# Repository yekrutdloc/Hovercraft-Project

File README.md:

# Line-following Hovercraft
School project embedded systems, web, Arduino

Functioning Hovercraft system

Contains documentation

Uses FreeRTOS, PID-library and Arduino

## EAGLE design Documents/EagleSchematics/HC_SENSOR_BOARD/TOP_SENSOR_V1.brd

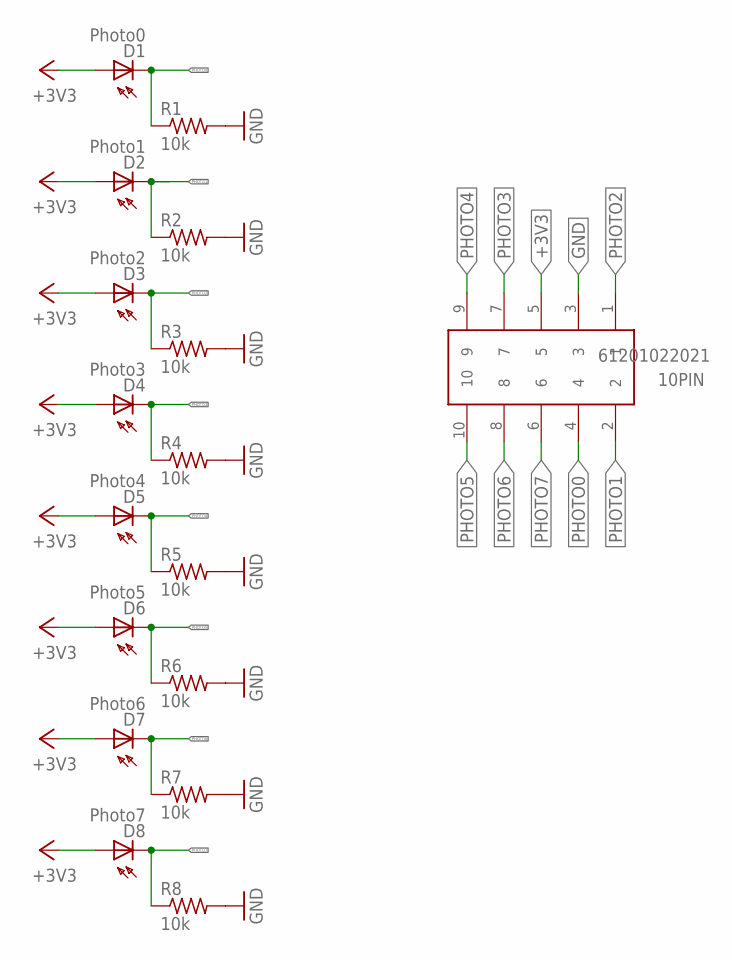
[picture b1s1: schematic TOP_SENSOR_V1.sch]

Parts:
10PIN: 61201022021
D1: Photo0; BPX65
D2: Photo1; BPX65
D3: Photo2; BPX65
D4: Photo3; BPX65
D5: Photo4; BPX65
D6: Photo5; BPX65
D7: Photo6; BPX65
D8: Photo7; BPX65
R1, R2, R3, R4, R5, R6, R7, R8: 10k; 0207/10

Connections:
+3V3: 10PIN.5, D1.A, D2.A, D3.A, D4.A, D5.A, D6.A, D7.A, D8.A
GND: 10PIN.3, R1.2, R2.2, R3.2, R4.2, R5.2, R6.2, R7.2, R8.2
PHOTO0: 10PIN.4, D1.K (C), R1.1
PHOTO1: 10PIN.2, D2.K (C), R2.1
PHOTO2: 10PIN.1, D3.K (C), R3.1
PHOTO3: 10PIN.7, D4.K (C), R4.1
PHOTO4: 10PIN.9, D5.K (C), R5.1
PHOTO5: 10PIN.10, D6.K (C), R6.1
PHOTO6: 10PIN.8, D7.K (C), R7.1
PHOTO7: 10PIN.6, D8.K (C), R8.1

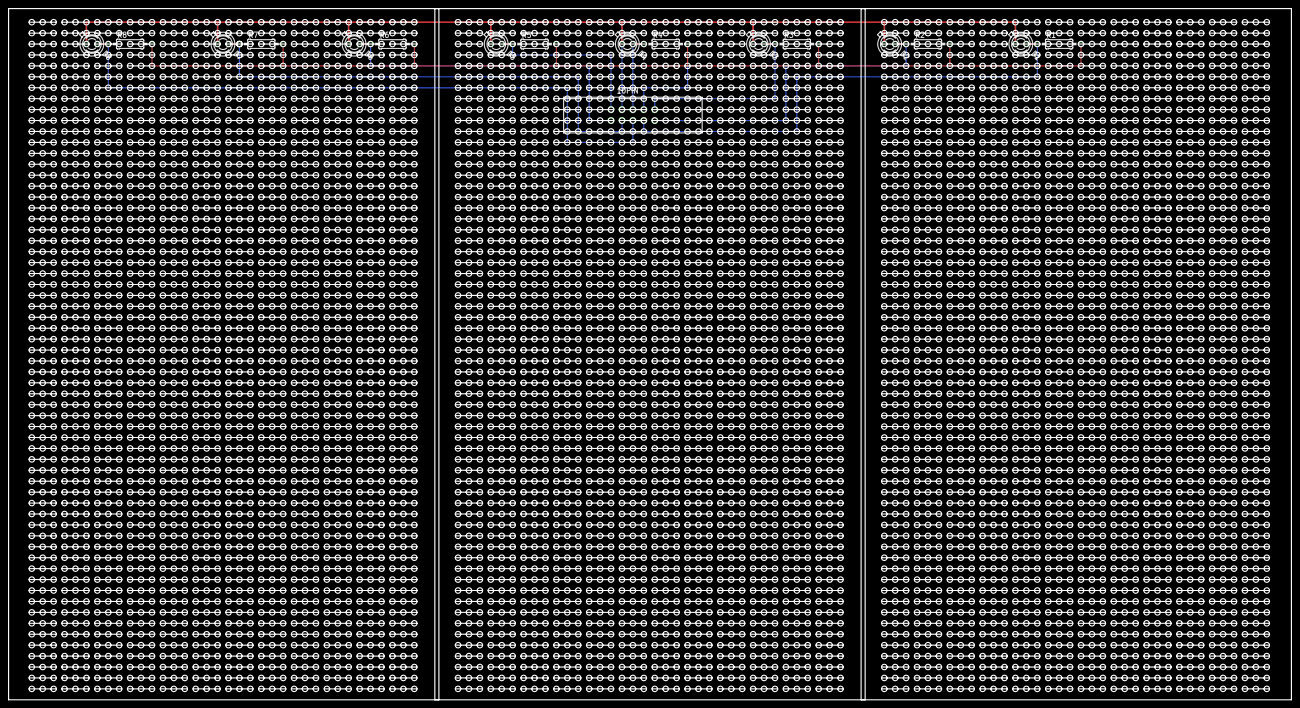
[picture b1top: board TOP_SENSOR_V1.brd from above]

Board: 2 copper layers, 298.1 x 160.6 mm, 17 parts (0 on the bottom side), 10 nets.

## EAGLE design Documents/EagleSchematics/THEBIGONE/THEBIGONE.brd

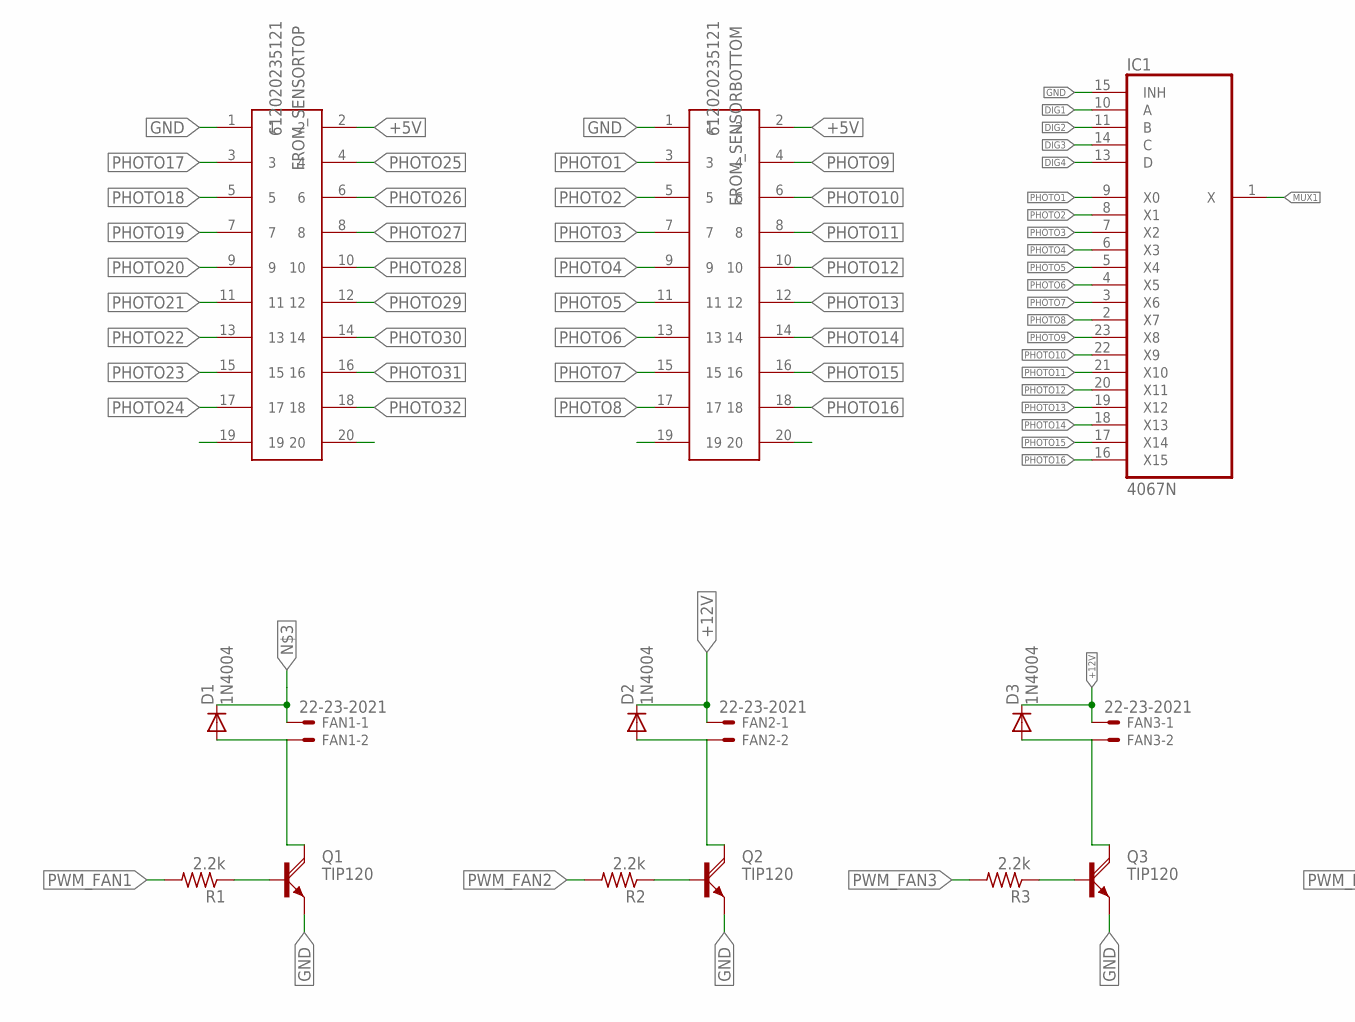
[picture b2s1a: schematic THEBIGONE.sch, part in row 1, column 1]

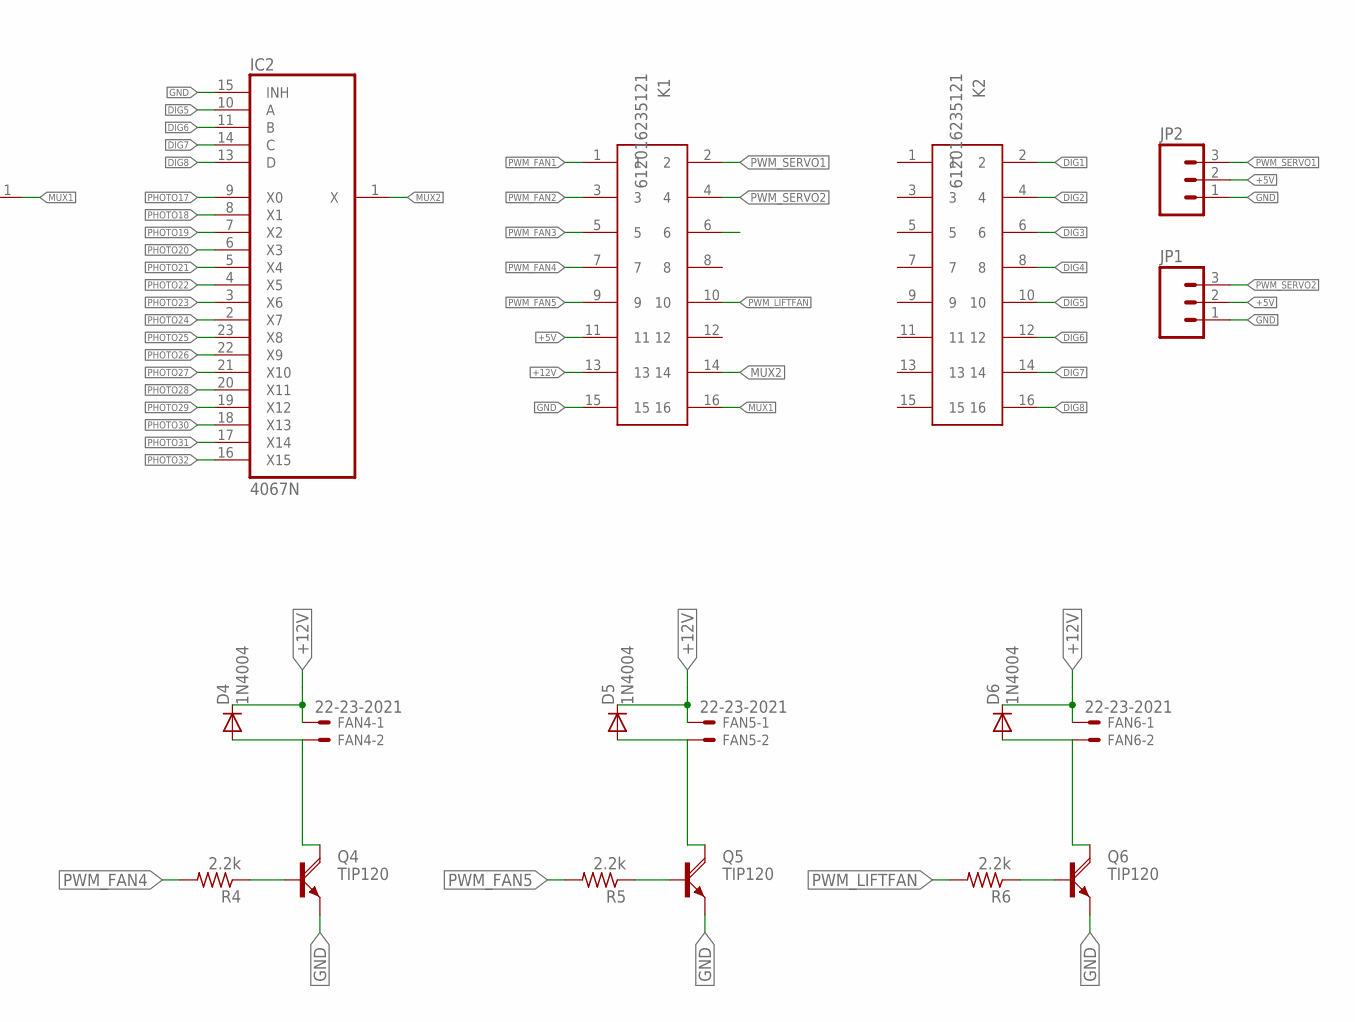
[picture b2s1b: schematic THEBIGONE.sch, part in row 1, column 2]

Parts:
D1, D2, D3, D4, D5, D6: 1N4004; DO41-10
FAN1, FAN2, FAN3, FAN4, FAN5, FAN6: 22-23-2021
FROM_SENSORBOTTOM: 612020235121
FROM_SENSORTOP: 612020235121
IC1, IC2: 4067N; DIL24-6
JP1, JP2: M03JST-PTH-VERT; JST-3-PTH-VERT
K1, K2: 612016235121
Q1, Q2, Q3, Q4, Q5, Q6: TIP120; TO220AH
R1, R2, R3, R4, R5, R6: 2.2k; 0204/7

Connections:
+5V: FROM_SENSORBOTTOM.2, FROM_SENSORTOP.2, JP1.2, JP2.2, K1.11
+12V: D1.C, D2.C, D3.C, FAN1.1, FAN2.1, FAN3.1, K1.13
DIG1: IC1.10 (A), K2.2
DIG2: IC1.11 (B), K2.4
DIG3: IC1.14 (C), K2.6
DIG4: IC1.13 (D), K2.8
DIG5: IC2.10 (A), K2.10
DIG6: IC2.11 (B), K2.12
DIG7: IC2.14 (C), K2.14
DIG8: IC2.13 (D), K2.16
GND: FROM_SENSORBOTTOM.1, FROM_SENSORTOP.1, IC1.15 (INH), IC2.15 (INH), JP1.1, JP2.1, K1.15, Q1.E, Q2.E, Q3.E, Q4.E, Q5.E, Q6.E
MUX1: IC1.1 (X), K1.16
MUX2: IC2.1 (X), K1.14
unnamed: D1.A, FAN1.2, Q1.C
unnamed: D2.A, FAN2.2, Q2.C
unnamed: Q1.B, R1.1
unnamed: Q2.B, R2.1
unnamed: D3.A, FAN3.2, Q3.C
unnamed: D4.A, FAN4.2, Q4.C
unnamed: D4.C, FAN4.1
unnamed: Q5.B, R5.1
unnamed: Q4.B, R4.1
unnamed: D5.A, FAN5.2, Q5.C
unnamed: D5.C, FAN5.1
unnamed: Q3.B, R3.1
unnamed: Q6.B, R6.1
unnamed: D6.A, FAN6.2, Q6.C
unnamed: D6.C, FAN6.1
PHOTO1: FROM_SENSORBOTTOM.3, IC1.9 (X0)
PHOTO2: FROM_SENSORBOTTOM.5, IC1.8 (X1)
PHOTO3: FROM_SENSORBOTTOM.7, IC1.7 (X2)
PHOTO4: FROM_SENSORBOTTOM.9, IC1.6 (X3)
PHOTO5: FROM_SENSORBOTTOM.11, IC1.5 (X4)
PHOTO6: FROM_SENSORBOTTOM.13, IC1.4 (X5)
PHOTO7: FROM_SENSORBOTTOM.15, IC1.3 (X6)
PHOTO8: FROM_SENSORBOTTOM.17, IC1.2 (X7)
PHOTO9: FROM_SENSORBOTTOM.4, IC1.23 (X8)
PHOTO10: FROM_SENSORBOTTOM.6, IC1.22 (X9)
PHOTO11: FROM_SENSORBOTTOM.8, IC1.21 (X10)
PHOTO12: FROM_SENSORBOTTOM.10, IC1.20 (X11)
PHOTO13: FROM_SENSORBOTTOM.12, IC1.19 (X12)
PHOTO14: FROM_SENSORBOTTOM.14, IC1.18 (X13)
PHOTO15: FROM_SENSORBOTTOM.16, IC1.17 (X14)
PHOTO16: FROM_SENSORBOTTOM.18, IC1.16 (X15)
PHOTO17: FROM_SENSORTOP.3, IC2.9 (X0)
PHOTO18: FROM_SENSORTOP.5, IC2.8 (X1)
PHOTO19: FROM_SENSORTOP.7, IC2.7 (X2)
PHOTO20: FROM_SENSORTOP.9, IC2.6 (X3)
PHOTO21: FROM_SENSORTOP.11, IC2.5 (X4)
PHOTO22: FROM_SENSORTOP.13, IC2.4 (X5)
PHOTO23: FROM_SENSORTOP.15, IC2.3 (X6)
PHOTO24: FROM_SENSORTOP.17, IC2.2 (X7)
PHOTO25: FROM_SENSORTOP.4, IC2.23 (X8)
PHOTO26: FROM_SENSORTOP.6, IC2.22 (X9)
PHOTO27: FROM_SENSORTOP.8, IC2.21 (X10)
PHOTO28: FROM_SENSORTOP.10, IC2.20 (X11)
PHOTO29: FROM_SENSORTOP.12, IC2.19 (X12)
PHOTO30: FROM_SENSORTOP.14, IC2.18 (X13)
PHOTO31: FROM_SENSORTOP.16, IC2.17 (X14)
PHOTO32: FROM_SENSORTOP.18, IC2.16 (X15)
PWM_FAN1: K1.1, R1.2
PWM_FAN2: K1.3, R2.2
PWM_FAN3: K1.5, R3.2
PWM_FAN4: K1.7, R4.2
PWM_FAN5: K1.9, R5.2
PWM_LIFTFAN: K1.10, R6.2
PWM_SERVO1: JP2.3, K1.2
PWM_SERVO2: JP1.3, K1.4
PWM_SERVO3: K1.6
VDD: IC1.24 (VDD), IC2.24 (VDD)
VSS: IC1.12 (VSS), IC2.12 (VSS)

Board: 2 copper layers, 32 parts (0 on the bottom side), 70 nets, no tracks yet.

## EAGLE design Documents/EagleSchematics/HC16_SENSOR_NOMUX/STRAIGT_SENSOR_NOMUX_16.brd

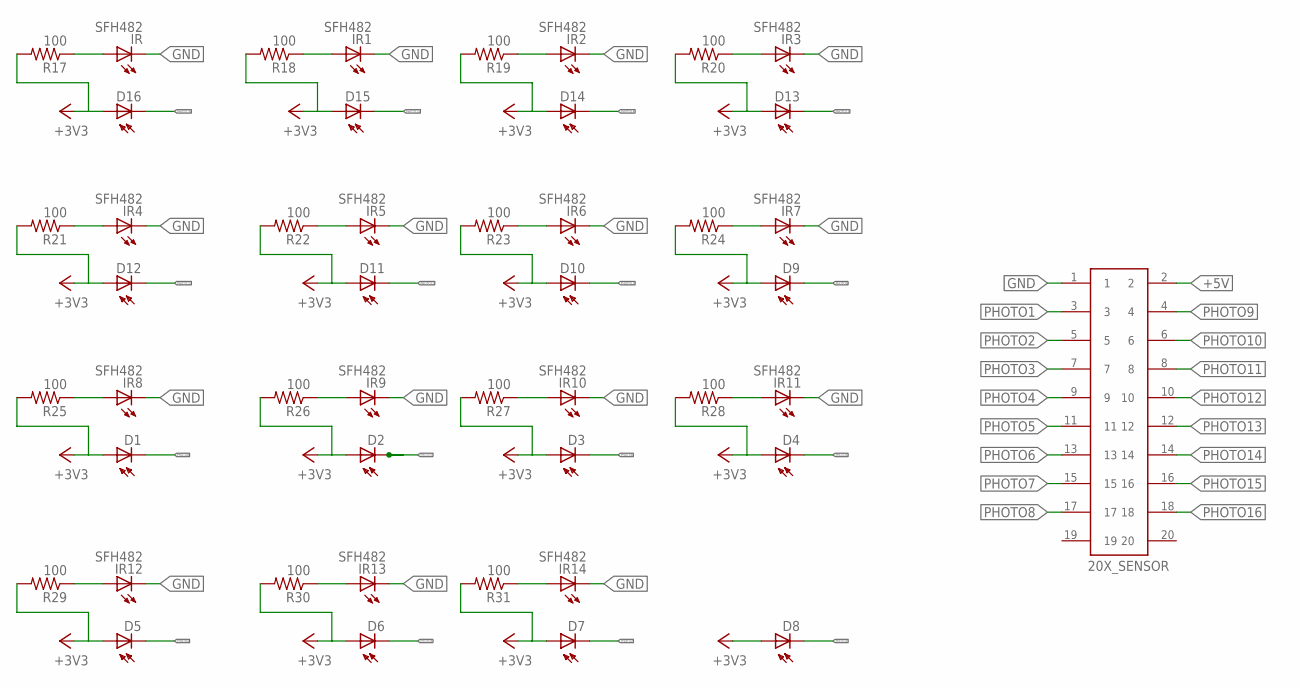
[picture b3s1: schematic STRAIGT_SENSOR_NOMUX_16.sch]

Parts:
20X_SENSOR: 61202022021
D1, D9, D10, D11, D12, D13, D14, D15, D16: Photo0; BPX65
D2: Photo1; BPX65
D3: Photo2; BPX65
D4: Photo3; BPX65
D5: Photo4; BPX65
D6: Photo5; BPX65
D7: Photo6; BPX65
D8: Photo7; BPX65
IR, IR1, IR2, IR3, IR4, IR5, IR6, IR7, IR8, IR9, IR10, IR11, IR12, IR13, IR14: SFH482
R17, R18, R19, R20, R21, R22, R23, R24, R25, R26, R27, R28, R29, R30, R31: 100; 0207/10

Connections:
+3V3: D1.A, D2.A, D3.A, D4.A, D5.A, D6.A, D7.A, D8.A, D9.A, D10.A, D11.A, D12.A, D13.A, D14.A, D15.A, D16.A, R17.2, R18.2, R19.2, R20.2, R21.2, R22.2, R23.2, R24.2, R25.2, R26.2, R27.2, R28.2, R29.2, R30.2, R31.2
+5V: 20X_SENSOR.2
GND: 20X_SENSOR.1, IR.K (C), IR1.K (C), IR2.K (C), IR3.K (C), IR4.K (C), IR5.K (C), IR6.K (C), IR7.K (C), IR8.K (C), IR9.K (C), IR10.K (C), IR11.K (C), IR12.K (C), IR13.K (C), IR14.K (C)
unnamed: IR1.A, R18.1
unnamed: IR.A, R17.1
unnamed: IR2.A, R19.1
unnamed: IR3.A, R20.1
unnamed: IR4.A, R21.1
unnamed: IR5.A, R22.1
unnamed: IR6.A, R23.1
unnamed: IR7.A, R24.1
unnamed: IR8.A, R25.1
unnamed: IR9.A, R26.1
unnamed: IR10.A, R27.1
unnamed: IR11.A, R28.1
unnamed: IR12.A, R29.1
unnamed: IR13.A, R30.1
unnamed: IR14.A, R31.1
PHOTO1: 20X_SENSOR.3, D8.K (C)
PHOTO2: 20X_SENSOR.5, D7.K (C)
PHOTO3: 20X_SENSOR.7, D6.K (C)
PHOTO4: 20X_SENSOR.9, D5.K (C)
PHOTO5: 20X_SENSOR.11, D4.K (C)
PHOTO6: 20X_SENSOR.13, D3.K (C)
PHOTO7: 20X_SENSOR.15, D2.K (C)
PHOTO8: 20X_SENSOR.17, D1.K (C)
PHOTO9: 20X_SENSOR.4, D9.K (C)
PHOTO10: 20X_SENSOR.6, D10.K (C)
PHOTO11: 20X_SENSOR.8, D11.K (C)
PHOTO12: 20X_SENSOR.10, D12.K (C)
PHOTO13: 20X_SENSOR.12, D13.K (C)
PHOTO14: 20X_SENSOR.14, D14.K (C)
PHOTO15: 20X_SENSOR.16, D15.K (C)
PHOTO16: 20X_SENSOR.18, D16.K (C)

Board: 2 copper layers, 47 parts (0 on the bottom side), 33 nets, no tracks yet.

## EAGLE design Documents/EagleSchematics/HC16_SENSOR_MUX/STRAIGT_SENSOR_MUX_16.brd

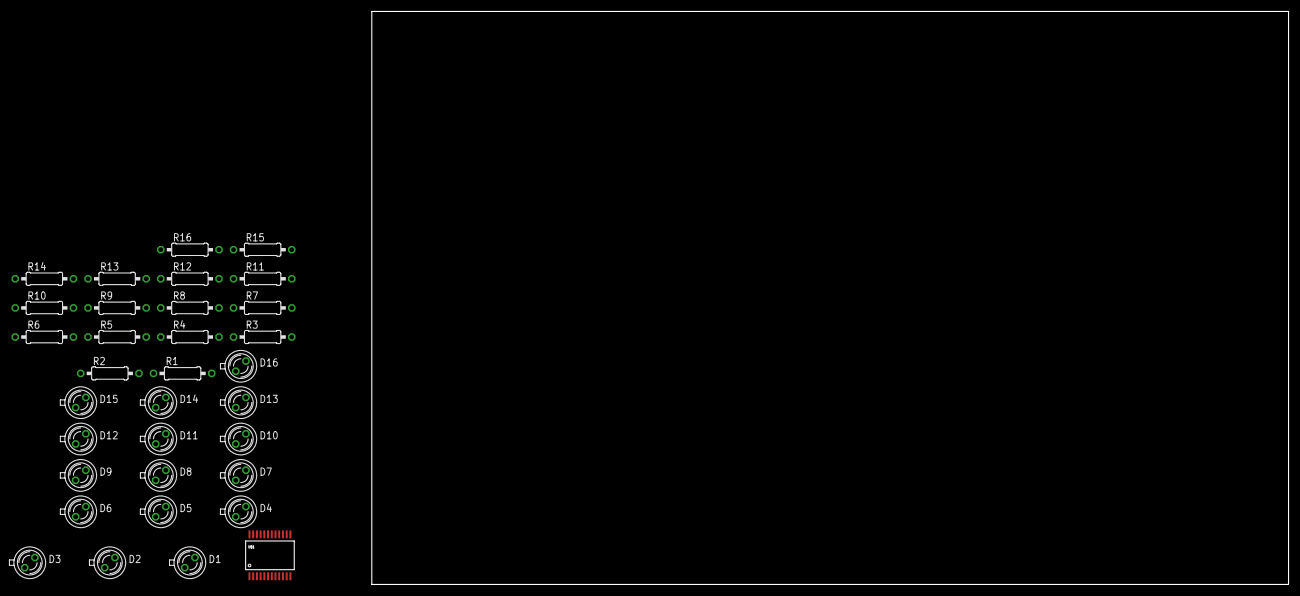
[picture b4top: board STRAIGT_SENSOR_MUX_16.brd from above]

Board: 2 copper layers, 160.0 x 100.0 mm, 33 parts (0 on the bottom side), 18 nets, no tracks yet.

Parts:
D1, D9, D10, D11, D12, D13, D14, D15, D16: Photo0; BPX65
D2: Photo1; BPX65
D3: Photo2; BPX65
D4: Photo3; BPX65
D5: Photo4; BPX65
D6: Photo5; BPX65
D7: Photo6; BPX65
D8: Photo7; BPX65
R1, R2, R3, R4, R5, R6, R7, R8, R9, R10, R11, R12, R13, R14, R15, R16: 10k; 0207/10
U$1: MUX-74HC4067SMD; SSOP24

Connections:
+3V3: D1.A, D2.A, D3.A, D4.A, D5.A, D6.A, D7.A, D8.A, D9.A, D10.A, D11.A, D12.A, D13.A, D14.A, D15.A, D16.A, U$1.24
GND: R1.2, R2.2, R3.2, R4.2, R5.2, R6.2, R7.2, R8.2, R9.2, R10.2, R11.2, R12.2, R13.2, R14.2, R15.2, R16.2, U$1.12, U$1.15
PHOTO1: D8.K, R8.1, U$1.9
PHOTO2: D7.K, R7.1, U$1.8
PHOTO3: D6.K, R6.1, U$1.7
PHOTO4: D5.K, R5.1, U$1.6
PHOTO5: D4.K, R4.1, U$1.5
PHOTO6: D3.K, R3.1, U$1.4
PHOTO7: D2.K, R2.1, U$1.3
PHOTO8: D1.K, R1.1, U$1.2
PHOTO9: D9.K, R9.1, U$1.23
PHOTO10: D10.K, R10.1, U$1.22
PHOTO11: D11.K, R11.1, U$1.21
PHOTO12: D12.K, R12.1, U$1.20
PHOTO13: D13.K, R13.1, U$1.19
PHOTO14: D14.K, R14.1, U$1.18
PHOTO15: D15.K, R15.1, U$1.17
PHOTO16: D16.K, R16.1, U$1.16

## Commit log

2014-03-31 4st fotoresistor test
2014-04-02 Kod för att testa servon
2014-04-03 påbörjan på linjesensorsystemet
2014-04-03 matlabsimulering för linjesensor tillagd
2014-04-04 updated LFC
2014-04-06 added 433MHz radio controlling for line follow calibration
2014-04-06 controlbox and line follow calibration update
    added basic controlbox 433mhz transmitter code and updated line follow
    calibration
2014-04-06 renamings
2014-04-06 small different changes to LFC
    updated comments and tidyed up code
2014-04-06 indent fixes
2014-04-06 added class diagram for lfm
2014-04-07 Controlbox update & patches to hovercraft program
    Added buttons to controlbox and fixed some bugs on hovercraft program
2014-04-07 updated use case diagram
2014-04-09 rewrote p2program
    Named the new program P2Program2.
    Also added datasheet for 433 MHz RT
2014-04-09 datasheet moved to folder
2014-04-09 Fan PWM-control
    Made a project being able to control PWM on a PWM-fan. Also added the
    pwm library to libraries folder and added the default PWM-fan sketch
2014-04-09 Reorganized the files
2014-04-11 tets
2014-04-11 tagit bort textfil
2014-04-11 Reorganized files to folders
2014-04-12 added docs for 433mhz
2014-04-14 testfeature commit
2014-04-14 testremoved
2014-04-14 Revert "testremoved"
    This reverts commit 5c17a87219ace2bbb2c654d73220319c4f064e1d.
2014-04-14 Revert 84be9a2..6728577
    This rolls back to commit 84be9a23fd9bc22c4ec5de6062d9929b1bbac040.
2014-04-14 test
    test
2014-04-14 Ta bort test.txt
2014-04-16 Added Eagle Schematics directory
    Eagle schematics for Sensor, Bus and Motherboards.
2014-04-16 Changed Eagle directory from Test to Documents
2014-04-22 EagleSchematics x16
    Sensorboard (100%)
    Busboard (90%)
    Motherboard (20%)
2014-04-24 Gyro
2014-04-24 rotate-Z
2014-04-28 added chibiOS library
2014-05-07 Eagle Schematics
    Changed array of sensornetwork
2014-05-09 Updated RCSwitch, UML, sorting and examples
    Added updated libraries for RCSwitch.
    Added example sketch for making classes in Arduino
    Sorted sketches into correct folders
    Updated UML
2014-05-10 Added THEBIGONE schematic
2014-05-11 Class diagram first version
2014-05-11 Started sequence diagram of "Following a track"
2014-05-12 Almost final version of schematics
    Updated BigBoard with the new design
2014-05-12 PWM control fan using analogWrite
2014-05-14 FIR-filter, ADC, ChiboOS test & Hovercraft dance
    Added library for potential chosen FIR-filter library.
    Added an example sketch for controlling ADC.
    Added example sketch for using ChibiOS with multiple threads. Make a
    Sketch to demonstrate movement on the hovercraft.
2014-05-15 Final
    Final schematics
2014-05-15 unit testing library
    added unit testing library for arduino ide
2014-05-15 Multiple tabs example sketch, arduinounit bugfix
    Added example sketch to demonstrate usage of multiple sketch source
    files(.ino)
    Fixed bug of arduinounit library where it would not be found by Arduino
    IDE.
2014-05-15 PID library added
2014-05-17 Added unit tests for M3
    Added unit test for multiplex and PIDLibrary
2014-05-17 Cleanup for M3
    Removed unused and unnecessary libraries and sketches
2014-05-17 Removed 433 MHz switch library
2014-05-17 Sketch renaming and reorganization
2014-05-18 Documentation, comments & renamings
    Documentation and comments finished for current programs
    Also some renaming of projects
2014-05-18 EagleSchematics clean-up
    Moved unused schematics and directories to "Deprecated" folder
2014-05-18 Integrated ChibiOS with Front Line Sensor System
2014-05-18 testhishmessage
2014-05-18 Visual Studio stuff
    Visual Micro stuff
2014-05-18 Git test from Git program
2014-05-18 Git test 2 from Git program
2014-05-19 Main Program with ChibiOS (Linesensor + Percent)
2014-05-19 SystemIntegration: Chib/PWM/Line
    MainProgram with Linesensor to Motor PID
2014-05-19 PID AutoTune Library, ChibiOS tests
    Added library for PID AutoTune library
    Made Sketch to unit test single multiplex channel
2014-05-20 Changed priorities of threads
2014-05-21 Added image description of Arduino Due pins
2014-05-21 Fixed corrupted files
    fixed corrupted files from Visual Studio project folder
2014-05-21 Deleted some uneeded files...
    Deleted some uneeded files… which hogged github
2014-05-21 Revert "Deleted some uneeded files..."
    This reverts commit c78fb0c7f483e89f27758b1691c7246809be1607.
2014-05-21 Revert "Changed priorities of threads"
    This reverts commit e32be2a6247e1859e4c7c506911b3d43b8c59855.
    Conflicts:
    Software/HoverCraftSystem/MainThread.ino
    Software/HoverCraftSystem/Visual Micro/.HoverCraftSystem.vsarduino.h
2014-05-21 Revert e32be2a..84731f0
    This rolls back to commit e32be2a6247e1859e4c7c506911b3d43b8c59855.
2014-05-21 Added Gyro and Arduino Due pinout
2014-05-21 Old Hovercraft stuff
2014-05-21 SDF/SUO
2014-05-21 mergeready
2014-05-21 some automatically created file needed to commit
2014-05-22 RIGHT + LEFT line motor control !with issues!
2014-05-22 Added multiplex files
2014-05-22 Converted to FreeRTOS
2014-05-22 Rebuilt hovercraftsystem from ground!
    -Converted from ChibiOS to FreeRTOS
    -Made front and rear line sensors work with code
    -Made front and rear PID-fans work
    -Added capability to calibrate front and rear line sensors via
    bluetooth commands!
    -Added ability to PWM-contro lift fan and forward propulsion fans
2014-05-22 Automatically created files
2014-05-22 Changed PWM on liftfan to 255
2014-05-25 Accelerometer calibration+velocity calculation
2014-05-25 Pre-cleanup with PID
2014-05-25 Accelerometer & velocity(Matlab+Sketch)
    Added Matlab plot for acceleration+velocity
    Renamed accelerometer+velocity Sketch
2014-05-26 Performance optimized hovercraft system.
    -Less threads, merged PID and motor controllers
    -Added new line sensor code
2014-05-26 Hovercraft system following line!!
    -First version to fully follow line
    -Alot of PID optimizations!
2014-05-26 Fixed bad calibration and steering
2014-05-26 Semaphores, performance optimizations
    -Added semaphore-PWM-change ability for forward propulsion
    -Performance optimizations
2014-05-26 Commit automatically created files
2014-05-26 Repaired HoverCraftSystem
2014-05-26 fixed some visual studio bugs
2014-05-27 Rebuilt project again because of VS xml-bugs
2014-05-27 Added freeRTOS library
    Also removed ChibiOS
2014-05-27 Reconstructed line sensor code
    Changed code to adapt to 5x loop
2014-05-27 After demonstration
2014-05-28 After second 9am calibration
2014-05-28 Hovercraftsystem:Class Diagram and Docs
    Created class diagram of HoverCraftSystem-program
    Documentet code of HoverCraftSystem
2014-05-28 Enhanced the hovecraftsystem documentation
2014-06-11 commented hovercraft system code with authors
2014-06-11 Added comments and authors for all testcode
2014-06-11 Final commenting and minor cleanup
2014-06-12 added sequence diagram for line sensor code
2014-08-22 Backning augusti

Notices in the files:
parts and their libraries:
SparkFun-AnalogIC: Licensing:Creative Commons ShareAlike 4.0 International - https://creativecommons.org/licenses/by-sa/4.0
Wuerth_Elektronik_eiCan_05_Box_Header_ID: Copyright: Würth Elektronik
